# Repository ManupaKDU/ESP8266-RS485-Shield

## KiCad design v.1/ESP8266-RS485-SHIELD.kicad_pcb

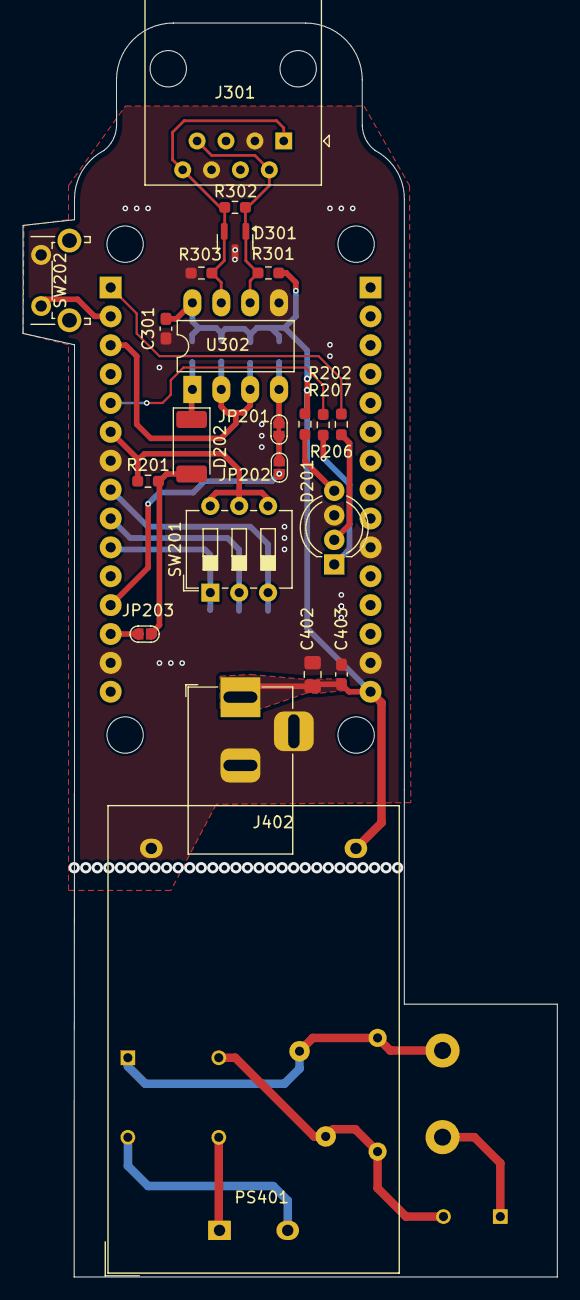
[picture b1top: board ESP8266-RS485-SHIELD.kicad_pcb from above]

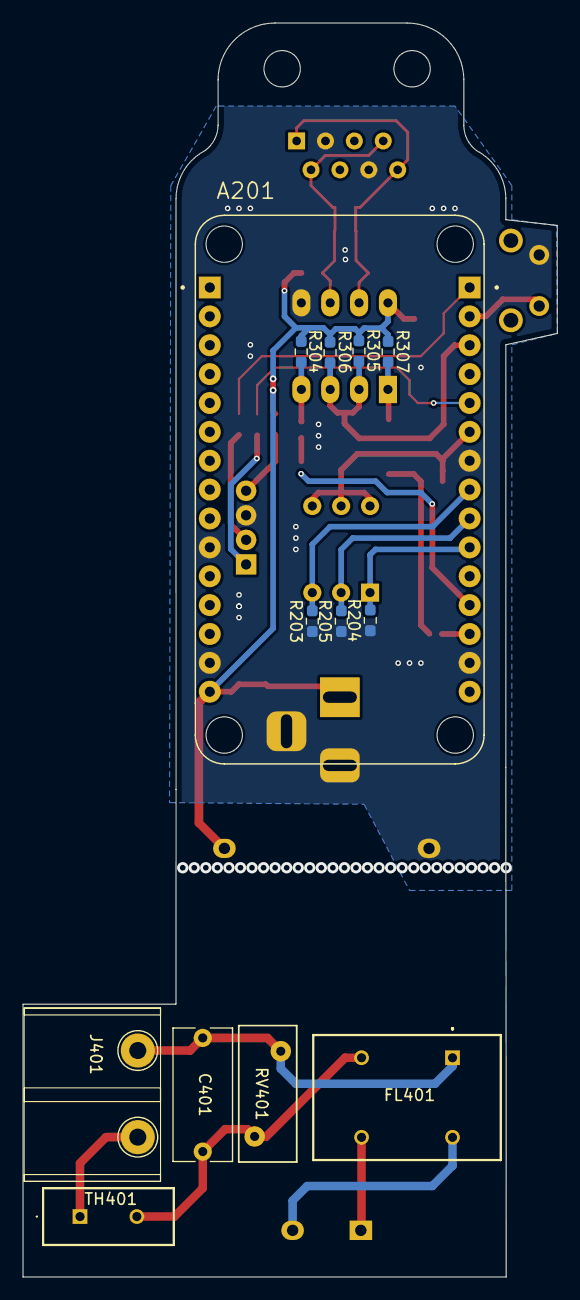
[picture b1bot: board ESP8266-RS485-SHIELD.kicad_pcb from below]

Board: 2 copper layers, 47.0 x 110.3 mm, 35 parts (13 on the bottom side), 26 nets.

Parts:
A201: 113990105; SEEED_113990105
C301, C403: 0.1MFD/16V; C_0603_1608Metric_Pad1.08x0.95mm_HandSolder
C401: 0.1MFD/250VAC; C_Rect_L11.5mm_W5.0mm_P10.00mm_MKT
C402: 10MFD/16V; C_0805_2012Metric_Pad1.18x1.45mm_HandSolder
D201: LED_BGKR; LED_D5.0mm-4_RGB_Wide_Pins
D202: 1N4148; D_MELF
D301: SM712_SOT23; SOT-23
FL401: 10mH; B82730U3951A020
J301: RJ45; RJ45_Amphenol_54602-x08_Horizontal
J401: 7.62mm 2-Pin Screw Terminal; P=7.62mm Barrier Terminal Blocks azend
J402: Barrel_Jack_Switch_Pin3Ring; BarrelJack_Horizontal
JP201: Jumper_2_Small_Bridged; small_jumper-bridged
JP202, JP203: SolderJumper_2_Open; small_jumper
PS401: HLK-5M05; Converter_ACDC_Hi-Link_HLK-5Mxx
R201, R202, R203, R204, R205, R301, R303, R304, R305, R306, R307: 10K; R_0603_1608Metric_Pad0.98x0.95mm_HandSolder
R206, R207: 1K; R_0603_1608Metric_Pad0.98x0.95mm_HandSolder
R302: 120R; R_0603_1608Metric_Pad0.98x0.95mm_HandSolder
RV401: 10D561; RV_Disc_D12mm_W5.1mm_P7.5mm
SW201: SW_DIP_x03; SW_DIP_SPSTx03_Slide_6.7x9.18mm_W7.62mm_P2.54mm_LowProfile
SW202: SW_Push; SW_Tactile_SPST_Angled_PTS645Vx39-2LFS
TH401: Thermistor; B57236S0250M000
U302: MAX485E; DIP-8_W7.62mm_LongPads

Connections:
+3V3: A201.J2_6 (3V3), A201.J2_15 (3V3), R201.1, SW201.4, SW201.5, SW201.6
+5V: A201.J1_15 (VIN), C301.1, C402.1, C403.1, J402.1, PS401.4 (+VO), R202.2, R301.2, R304.2, R305.2, R306.2, R307.2, U302.8 (VCC)
/ESP8266-devkit/BTN_CONN: A201.J2_2 (D1), SW202.1
/ESP8266-devkit/DIP_1: A201.J2_8 (D5), R203.2, SW201.3
/ESP8266-devkit/DIP_2: A201.J2_9 (D6), R205.2, SW201.2
/ESP8266-devkit/DIP_3: A201.J2_10 (D7), R204.2, SW201.1
/ESP8266-devkit/LED_1: A201.J2_1 (D0), R206.2
/ESP8266-devkit/LED_2: A201.J2_5 (D4), R207.2
/ESP8266-devkit/RXD: D202.2 (A), JP203.2 (B), R201.2
/ESP8266-devkit/TXD: JP201.1 (A), JP202.2 (B)
A: D301.1 (A1), J301.2, J301.7, R301.1, R302.1, U302.6 (A)
B: D301.2 (A2), J301.1, J301.8, R302.2, R303.1, U302.7 (B)
DE-485: A201.J2_3 (D2), R305.1, R306.1, U302.2 (~RE), U302.3 (DE)
GND: A201.J1_10 (GND), A201.J1_14 (GND), A201.J2_7 (GND), A201.J2_14 (GND), C301.2, C402.2, C403.2, D201.3 (K), D301.3 (common), J301.3, J301.6, J402.2, J402.3, PS401.3 (-VO), R203.1, R204.1, R205.1, R303.2, SW202.2, U302.5 (GND)
unnamed: A201.J2_12 (D9), JP202.1 (A)
unnamed: A201.J2_13 (D10), JP203.1 (A)
unnamed: C401.1, FL401.2, RV401.2, TH401.2
unnamed: D201.1 (BA), R207.1
unnamed: D201.2 (GA), R206.1
unnamed: D201.4 (RA), R202.1
unnamed: C401.2, FL401.1, J401.1, RV401.1
unnamed: J401.2, TH401.1
unnamed: FL401.3, PS401.1 (AC_1)
unnamed: FL401.4, PS401.2 (AC_2)
RX-485: D202.1 (K), R307.1, U302.1 (RO)
TX-485: JP201.2 (B), R304.1, U302.4 (DI)

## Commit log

2024-06-10 Intial Commit
2024-06-10 Final Commit
    Added Schematics, PCB and gerber files
